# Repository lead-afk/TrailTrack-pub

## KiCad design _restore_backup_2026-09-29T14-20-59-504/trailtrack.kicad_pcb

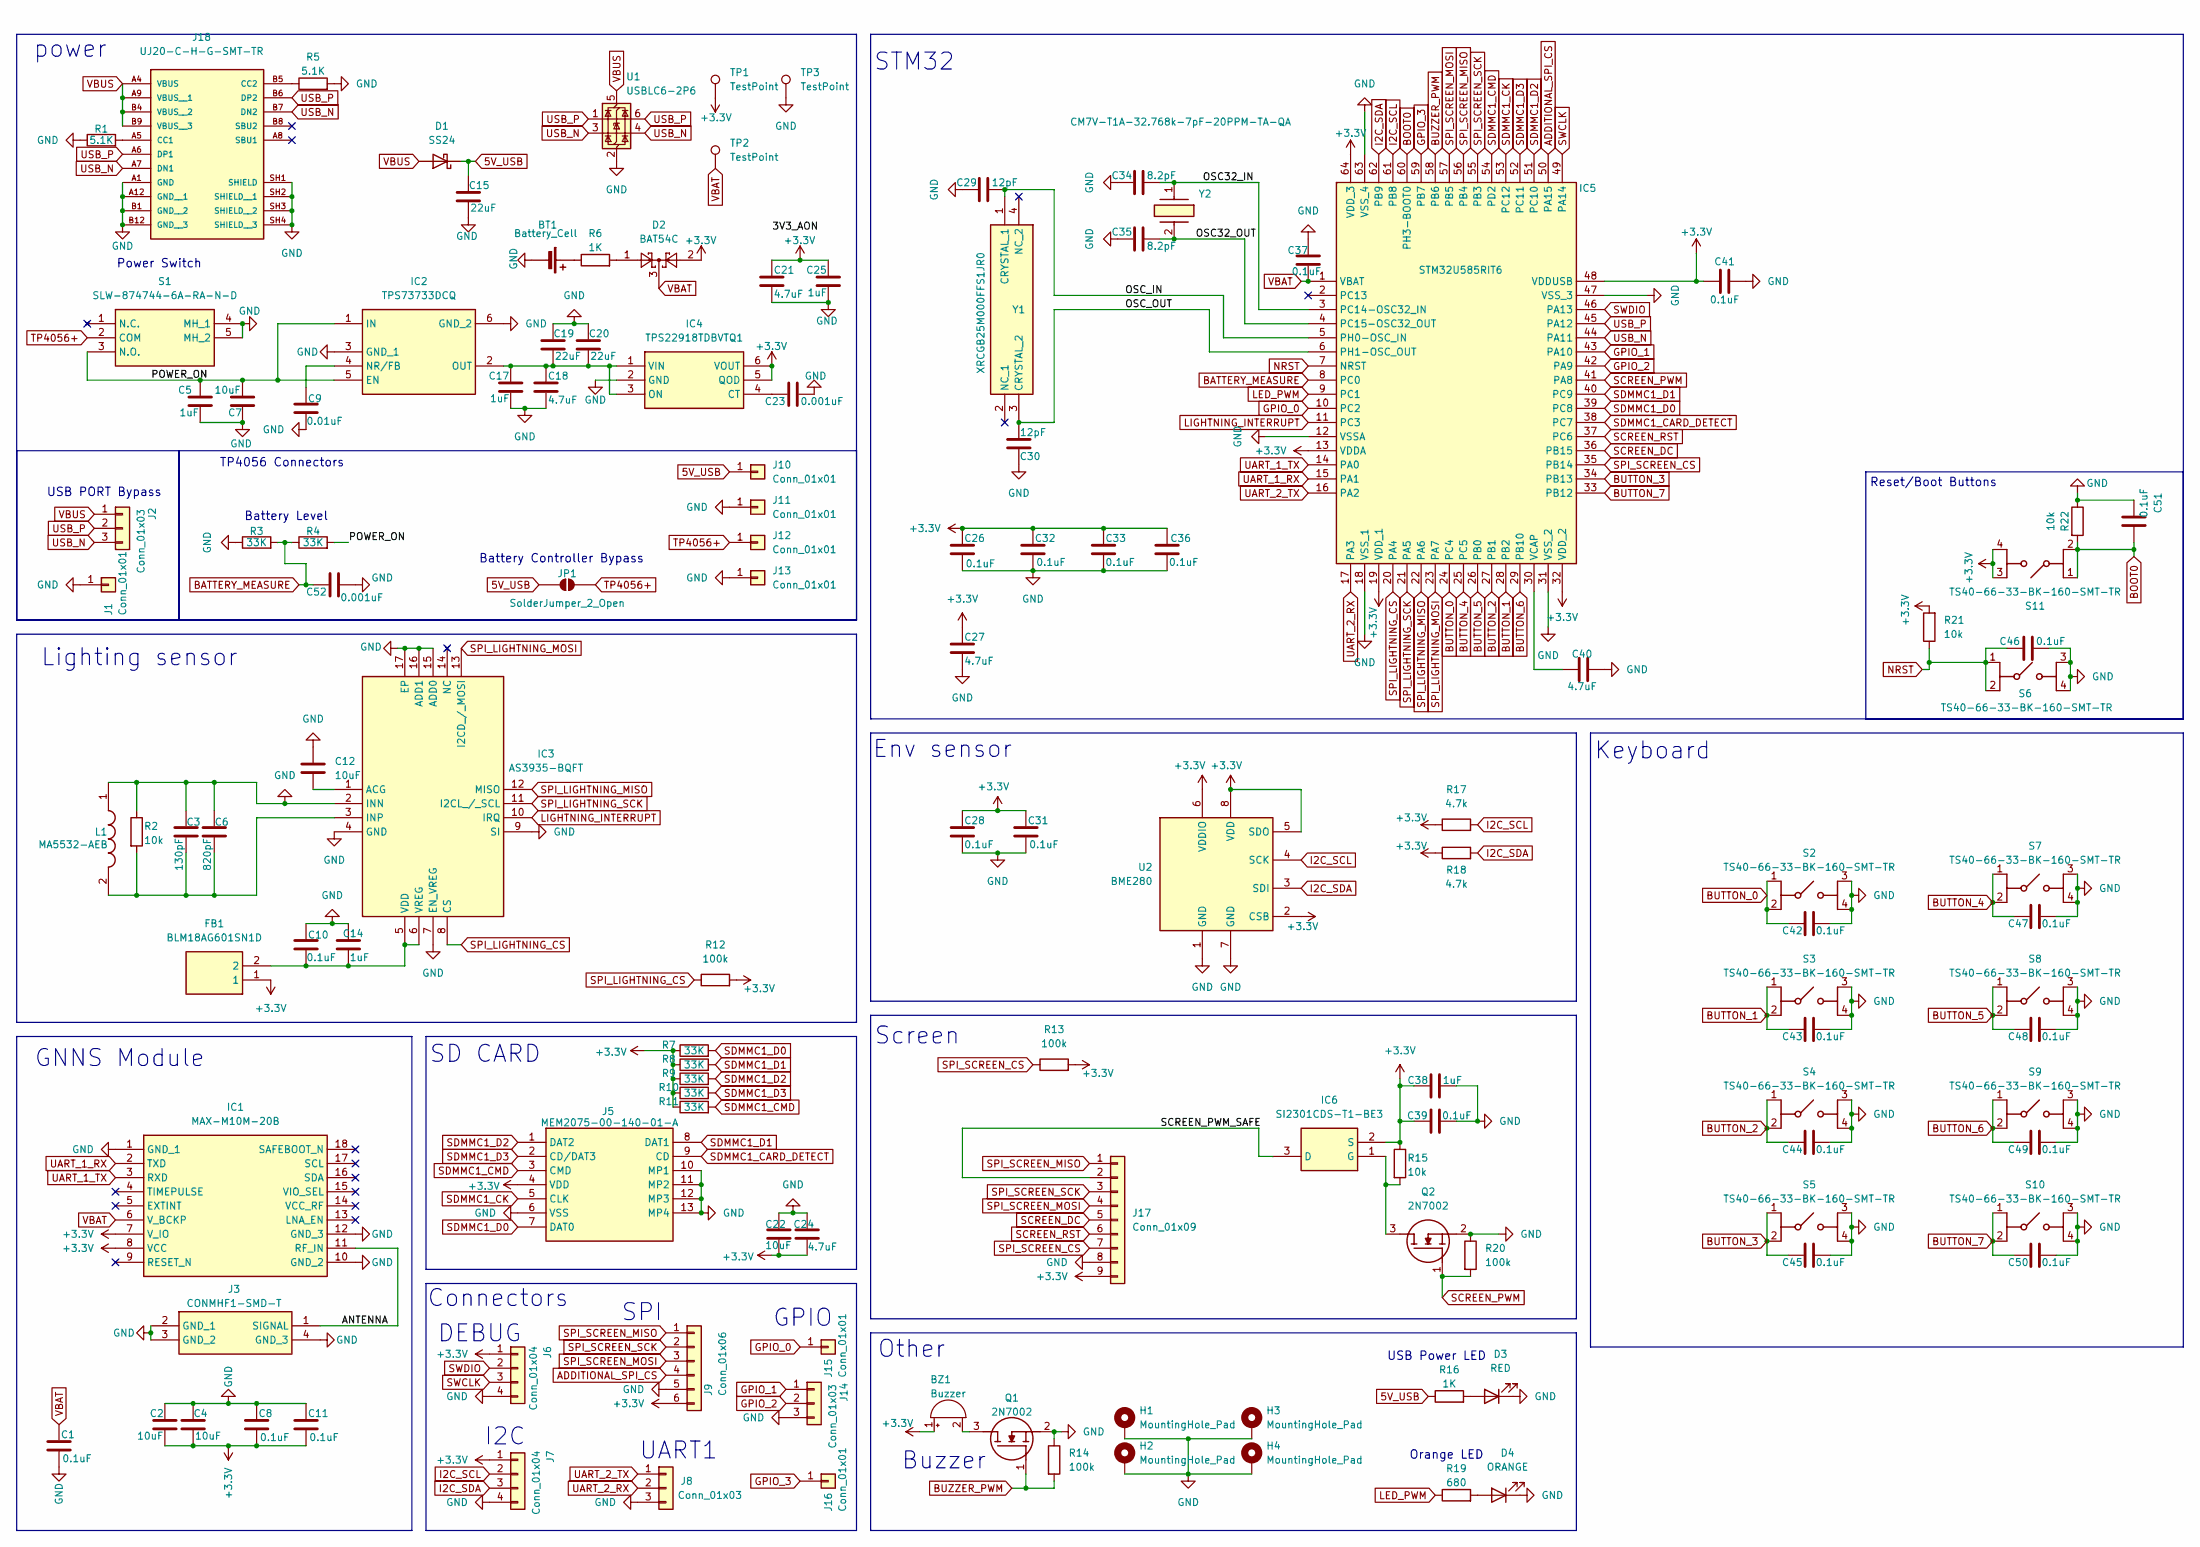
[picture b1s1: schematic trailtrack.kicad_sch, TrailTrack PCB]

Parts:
BT1: Battery_Cell; 1052; Mouser Part Number 534-1052-BH
BZ1: Buzzer; Buzzer_15x7.5RM7.6
C1, C8, C10, C11, C26, C28, C31, C32, C33, C36, C37, C39, C41, C42, C43, C44, C45, C46, C47, C48, C49, C50, C51: 0.1uF; C_0805_2012Metric; Mouser Part Number 81-GCM21BR71E104JA7L
C2, C4, C7, C12, C22: 10uF; C_0805_2012Metric; Mouser Part Number 81-GRM21BC81A106KE8L
C3: 130pF; C_0805_2012Metric; Mouser Part Number 81-GQM21952E131GB12D
C5, C14, C17, C25, C38: 1uF; C_0805_2012Metric; Mouser Part Number 81-GRM40X105K10K
C6: 820pF; C_0805_2012Metric; Mouser Part Number 81-RM21A5C2E821FWA1J
C9: 0.01uF; C_0805_2012Metric; Mouser Part Number 81-GCM2195C1K103FA6D
C15, C19, C20: 22uF; C_0805_2012Metric; Mouser Part Number 81-GRM21BC81A226ME4L
C18, C21, C24, C27, C40: 4.7uF; C_0805_2012Metric; Mouser Part Number 81-GCM21BR71C475KA3L
C23, C52: 0.001uF; C_0805_2012Metric; Mouser Part Number 81-GRM21R72A102JA01D
C29, C30: 12pF; C_0603_1608Metric; Mouser Part Number 81-GCM1885C2A120FA6D
C34, C35: 8.2pF; C_0603_1608Metric; Mouser Part Number 81-GCM1885C2A8R2BA6D
D1: SS24; DIOM5436X244N; Mouser Part Number 821-SS24
D2: BAT54C; SOT-23; Mouser Part Number 637-BAT54C
D3: RED; LED_0805_2012Metric; Mouser Part Number 630-HSMS-C170
D4: ORANGE; LED_0805_2012Metric; Mouser Part Number 630-HSMD-C170
FB1: BLM18AG601SN1D; BLM18SP221SN1B; Mouser Part Number 81-BLM11A601S
H1, H2, H3, H4: MountingHole_Pad; MountingHole_3.2mm_M3_DIN965_Pad
IC1: MAX-M10M-20B; MAXM10M20B; Mouser Part Number 377-MAX-M10M-20B
IC2: TPS73733DCQ; SOT127P706X180-6N; Mouser Part Number 595-TPS73733DCQ
IC3: AS3935-BQFT; QFN65P400X400X80-17N-D; Mouser Part Number 985-AS3935-BQFT
IC4: TPS22918TDBVTQ1; SOT95P280X145-6N; Mouser Part Number 595-TPS22918TDBVTQ1
IC5: STM32U585RIT6; QFP50P1200X1200X160-64N; Mouser Part Number 511-STM32U585RIT6
IC6: SI2301CDS-T1-BE3; SOT95P237X112-3N; Mouser Part Number 78-SI2301CDS-T1-BE3
J1, J10, J11, J12, J13, J15, J16: Conn_01x01; PinHeader_1x01_P2.54mm_Vertical
J2, J8: Conn_01x03; PinHeader_1x03_P2.54mm_Vertical
J3: CONMHF1-SMD-T; CONMHF1SMDT; Mouser Part Number 712-CONMHF1-SMD-T
J5: MEM2075-00-140-01-A; MEM20750014001A; Mouser Part Number 640-MEM20750014001A
J6, J7: Conn_01x04; PinHeader_1x04_P2.54mm_Vertical
J9: Conn_01x06; PinHeader_1x06_P2.54mm_Vertical
J14: Conn_01x03; PinHeader_1x03_P1.27mm_Vertical
J17: Conn_01x09; PinSocket_1x09_P2.54mm_Vertical
J18: UJ20-C-H-G-SMT-TR; CUI_UJ20-C-H-G-SMT-TR; PARTREV 1.01
JP1: SolderJumper_2_Open; SolderJumper-2_P1.3mm_Open_RoundedPad1.0x1.5mm
L1: MA5532-AEB; MA5532AEB; Mouser Part Number 994-MA5532-AE
Q1, Q2: 2N7002; SOT96P240X120-3N; Mouser Part Number 512-2N7002
R1, R5: 5.1K; R_0805_2012Metric; Mouser Part Number 603-RC0805FR-075K1L
R2, R15, R21, R22: 10k; R_0805_2012Metric; Mouser Part Number 603-AC0805DR-0710KL
R3, R4, R7, R8, R9, R10, R11: 33K; R_0805_2012Metric; Mouser Part Number 603-AC0805FR-0733KL
R6, R16: 1K; R_0805_2012Metric; Mouser Part Number 603-AC0805DR-071KL
R12, R13, R14, R20: 100k; R_0805_2012Metric; Mouser Part Number 603-AC0805FR-7W100KL
R17, R18: 4.7k; R_0805_2012Metric; Mouser Part Number 603-AC0805FR-7W4K7L
R19: 680; R_0805_2012Metric; Mouser Part Number 603-AC0805FR-07680RL
S1: SLW-874744-6A-RA-N-D; SLW8747446ARAND; Mouser Part Number 179-SLW8747446ARAND
S2, S3, S4, S5, S6, S7, S8, S9, S10, S11: TS40-66-33-BK-160-SMT-TR; TS406650R260SMTTR; Mouser Part Number 179-TS406633BK160S
TP1, TP2, TP3: TestPoint; TestPoint_Pad_D1.5mm
U1: USBLC6-2P6; SOT-666; Mouser Part Number 511-USBLC6-2P6
U2: BME280; Bosch_LGA-8_2.5x2.5mm_P0.65mm_ClockwisePinNumbering; Mouser Part Number 262-BME280
Y1: XRCGB25M000FFS1JR0; Mouser Part Number 81-XRCGB25M00FFS1JR0
Y2: CM7V-T1A-32.768k-7pF-20PPM-TA-QA; CM7V32768TBQA020; Mouser Part Number 428-201567-MG01

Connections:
5V_USB: C15.1, D1.1 (K), J10.1 (Pin_1_1), JP1.1 (A), R16.1
+3.3V: BZ1.1 (+), C2.2, C4.2, C8.2, C11.2, C21.1, C22.2, C24.2, C25.1, C26.1, C27.1, C28.1, C31.1, C32.1, C33.1, C36.1, C38.2, C39.2, C41.1, D2.2, FB1.1, IC1.7 (V_IO), IC1.8 (VCC), IC4.5 (QOD), IC4.6 (VOUT), IC5.13 (VDDA), IC5.19 (VDD_1), IC5.32 (VDD_2), IC5.48 (VDDUSB), IC5.64 (VDD_3), IC6.2 (S), J5.4 (VDD), J6.1, J7.1, J9.6, J17.9, R7.1, R8.1, R9.1, R10.1, R11.1, R12.2, R13.2, R15.1, R17.1, R18.1, R21.2, S11.3 (NO_1), S11.4 (NO_2), TP1.1 (1_1), U2.2 (CSB), U2.5 (SDO), U2.6 (VDDIO), U2.8 (VDD)
/ANTENNA: IC1.11 (RF_IN), J3.1 (SIGNAL)
/OSC32_IN: C34.2, IC5.3 (PC14-OSC32_IN), Y2.1
/OSC32_OUT: C35.2, IC5.4 (PC15-OSC32_OUT), Y2.2
/OSC_IN: C29.1, IC5.5 (PH0-OSC_IN), Y1.1 (CRYSTAL_1)
/OSC_OUT: C30.1, IC5.6 (PH1-OSC_OUT), Y1.3 (CRYSTAL_2)
/POWER_ON: C5.1, C7.2, IC2.1 (IN), IC2.5 (EN), R4.2, S1.3 (N.O.)
/SCREEN_PWM_SAFE: IC6.3 (D), J17.2
ADDITIONAL_SPI_CS: IC5.50 (PA15), J9.4
BATTERY_MEASURE: C52.2, IC5.8 (PC0), R3.2, R4.1
BOOT0: C51.2, IC5.60 (PH3-BOOT0), R22.2, S11.1 (COM_1), S11.2 (COM_2)
BUTTON_0: C42.1, IC5.24 (PC4), S2.1 (COM_1), S2.2 (COM_2)
BUTTON_1: C43.1, IC5.28 (PB2), S3.1 (COM_1), S3.2 (COM_2)
BUTTON_2: C44.1, IC5.27 (PB1), S4.1 (COM_1), S4.2 (COM_2)
BUTTON_3: C45.1, IC5.34 (PB13), S5.1 (COM_1), S5.2 (COM_2)
BUTTON_4: C47.1, IC5.25 (PC5), S7.1 (COM_1), S7.2 (COM_2)
BUTTON_5: C48.1, IC5.26 (PB0), S8.1 (COM_1), S8.2 (COM_2)
BUTTON_6: C49.1, IC5.29 (PB10), S9.1 (COM_1), S9.2 (COM_2)
BUTTON_7: C50.1, IC5.33 (PB12), S10.1 (COM_1), S10.2 (COM_2)
BUZZER_PWM: IC5.58 (PB6), Q1.1 (G), R14.2
GND: BT1.2 (-), C1.2, C2.1, C3.1, C4.1, C5.2, C6.1, C7.1, C8.1, C9.1, C10.2, C11.1, C12.1, C14.2, C15.2, C17.2, C18.2, C19.1, C20.1, C21.2, C22.1, C23.1, C24.1, C25.2, C26.2, C27.2, C28.2, C29.2, C30.2, C31.2, C32.2, C33.2, C34.1, C35.1, C36.2, C37.1, C38.1, C39.1, C40.2, C41.2, C42.2, C43.2, C44.2, C45.2, C46.2, C47.2, C48.2, C49.2, C50.2, C51.1, C52.1, D3.1 (K), D4.1 (K), H1.1 (1_1), H2.1 (1_1), H3.1 (1_1), H4.1 (1_1), IC1.1 (GND_1), IC1.10 (GND_2), IC1.12 (GND_3), IC2.3 (GND_1), IC2.6 (GND_2), IC3.2 (INN), IC3.4 (GND), IC3.7 (EN_VREG), IC3.9 (SI), IC3.15 (ADD0), IC3.16 (ADD1), IC3.17 (EP), IC4.2 (GND), IC5.12 (VSSA), IC5.18 (VSS_1), IC5.31 (VSS_2), IC5.47 (VSS_3), IC5.63 (VSS_4), J1.1 (Pin_1_1), J3.2 (GND_1), J3.3 (GND_2), J3.4 (GND_3), J5.6 (VSS), J5.10 (MP1), J5.11 (MP2), J5.12 (MP3), J5.13 (MP4), J6.4, J7.4, J8.3, J9.5, J11.1 (Pin_1_1), J13.1 (Pin_1_1), J14.3, J17.8, J18.A1 (GND), J18.A12 (GND__1), J18.B1 (GND__2), J18.B12 (GND__3), J18.SH1 (SHIELD), J18.SH2 (SHIELD__1), J18.SH3 (SHIELD__2), J18.SH4 (SHIELD__3), L1.1, Q1.2 (S), Q2.2 (S), R1.1, R2.1, R3.1, R5.2, R14.1, R20.1, R22.1, S1.4 (MH_1), S1.5 (MH_2), S2.3 (NO_1), S2.4 (NO_2), S3.3 (NO_1), S3.4 (NO_2), S4.3 (NO_1), S4.4 (NO_2), S5.3 (NO_1), S5.4 (NO_2), S6.3 (NO_1), S6.4 (NO_2), S7.3 (NO_1), S7.4 (NO_2), S8.3 (NO_1), S8.4 (NO_2), S9.3 (NO_1), S9.4 (NO_2), S10.3 (NO_1), S10.4 (NO_2), TP3.1 (1_1), U1.2 (GND), U2.1 (GND), U2.7 (GND)
GPIO_0: IC5.10 (PC2), J15.1 (Pin_1_1)
GPIO_1: IC5.43 (PA10), J14.1
GPIO_2: IC5.42 (PA9), J14.2
GPIO_3: IC5.59 (PB7), J16.1 (Pin_1_1)
I2C_SCL: IC5.61 (PB8), J7.2, R17.2, U2.4 (SCK)
I2C_SDA: IC5.62 (PB9), J7.3, R18.2, U2.3 (SDI)
LED_PWM: IC5.9 (PC1), R19.1
LIGHTNING_INTERRUPT: IC3.10 (IRQ), IC5.11 (PC3)
NRST: C46.1, IC5.7 (NRST), R21.1, S6.1 (COM_1), S6.2 (COM_2)
unnamed: BT1.1 (+), R6.1
unnamed: BZ1.2 (-), Q1.3 (D)
unnamed: D2.1, R6.2
unnamed: D3.2 (A), R16.2
unnamed: D4.2 (A), R19.2
unnamed: C9.2, IC2.4 (NR/FB)
unnamed: C17.1, C18.1, C19.2, C20.2, IC2.2 (OUT), IC4.1 (VIN), IC4.3 (ON)
unnamed: C12.2, IC3.1 (ACG)
unnamed: C3.2, C6.2, IC3.3 (INP), L1.2, R2.2
unnamed: C10.1, C14.1, FB1.2, IC3.5 (VDD), IC3.6 (VREG)
unnamed: C23.2, IC4.4 (CT)
unnamed: C40.1, IC5.30 (VCAP)
unnamed: IC6.1 (G), Q2.3 (D), R15.2
unnamed: J18.A5 (CC1), R1.2
unnamed: J18.B5 (CC2), R5.1
SCREEN_DC: IC5.36 (PB15), J17.5
SCREEN_PWM: IC5.41 (PA8), Q2.1 (G), R20.2
SCREEN_RST: IC5.37 (PC6), J17.6
SDMMC1_CARD_DETECT: IC5.38 (PC7), J5.9 (CD)
SDMMC1_CK: IC5.53 (PC12), J5.5 (CLK)
SDMMC1_CMD: IC5.54 (PD2), J5.3 (CMD), R11.2
SDMMC1_D0: IC5.39 (PC8), J5.7 (DAT0), R7.2
SDMMC1_D1: IC5.40 (PC9), J5.8 (DAT1), R8.2
SDMMC1_D2: IC5.51 (PC10), J5.1 (DAT2), R9.2
SDMMC1_D3: IC5.52 (PC11), J5.2 (CD/DAT3), R10.2
SPI_LIGHTNING_CS: IC3.8 (CS), IC5.20 (PA4), R12.1
SPI_LIGHTNING_MISO: IC3.12 (MISO), IC5.22 (PA6)
SPI_LIGHTNING_MOSI: IC3.13 (I2CD_/_MOSI), IC5.23 (PA7)
SPI_LIGHTNING_SCK: IC3.11 (I2CL_/_SCL), IC5.21 (PA5)
SPI_SCREEN_CS: IC5.35 (PB14), J17.7, R13.1
SPI_SCREEN_MISO: IC5.56 (PB4), J9.1, J17.1
SPI_SCREEN_MOSI: IC5.57 (PB5), J9.3, J17.4
SPI_SCREEN_SCK: IC5.55 (PB3), J9.2, J17.3
SWCLK: IC5.49 (PA14), J6.3
SWDIO: IC5.46 (PA13), J6.2
TP4056+: J12.1 (Pin_1_1), JP1.2 (B), S1.2 (COM)
UART_1_RX: IC1.2 (TXD), IC5.15 (PA1)
UART_1_TX: IC1.3 (RXD), IC5.14 (PA0)
UART_2_RX: IC5.17 (PA3), J8.2
UART_2_TX: IC5.16 (PA2), J8.1
USB_N: IC5.44 (PA11), J2.3, J18.A7 (DN1), J18.B7 (DN2), U1.3 (I/O2), U1.4 (I/O2)
USB_P: IC5.45 (PA12), J2.2, J18.A6 (DP1), J18.B6 (DP2), U1.1 (I/O1), U1.6 (I/O1)
VBAT: C1.1, C37.2, D2.3, IC1.6 (V_BCKP), IC5.1 (VBAT), TP2.1 (1_1)
VBUS: D1.2 (A), J2.1, J18.A4 (VBUS), J18.A9 (VBUS__1), J18.B4 (VBUS__2), J18.B9 (VBUS__3), U1.5 (VBUS)

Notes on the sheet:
Keyboard
UART1
SD CARD
Screen
GPIO
I2C
TP4056 Connectors
SPI
Battery Controller Bypass
USB Power LED
GNNS Module
Power Switch
STM32
Other
power
DEBUG
Env sensor
Lighting sensor
USB PORT Bypass
Buzzer
Orange LED
Connectors
Reset/Boot Buttons
Battery Level

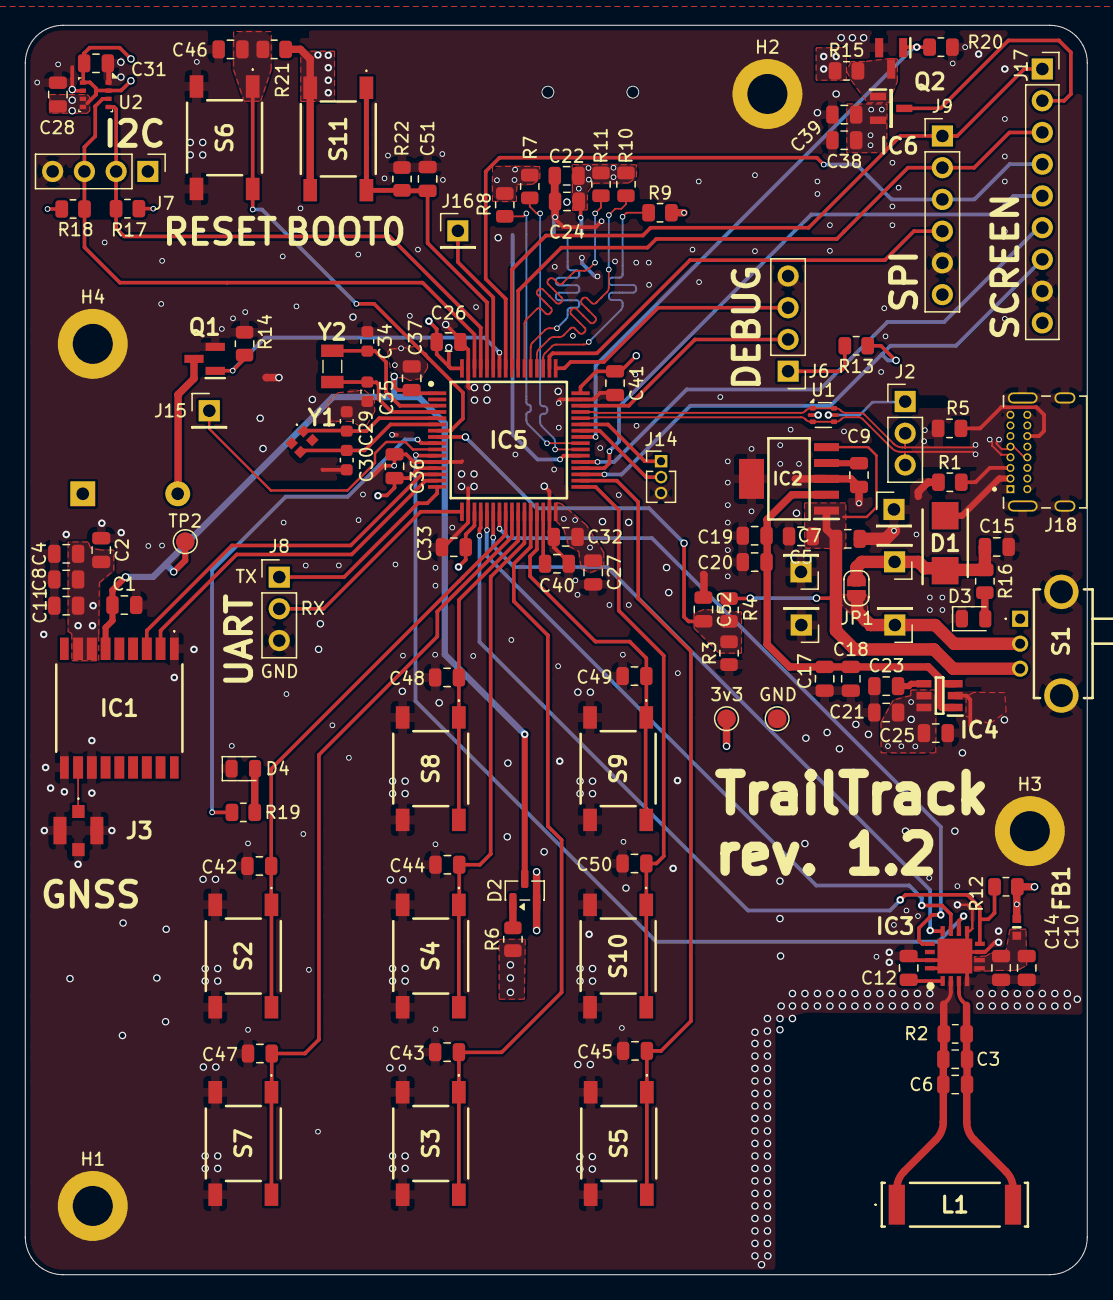
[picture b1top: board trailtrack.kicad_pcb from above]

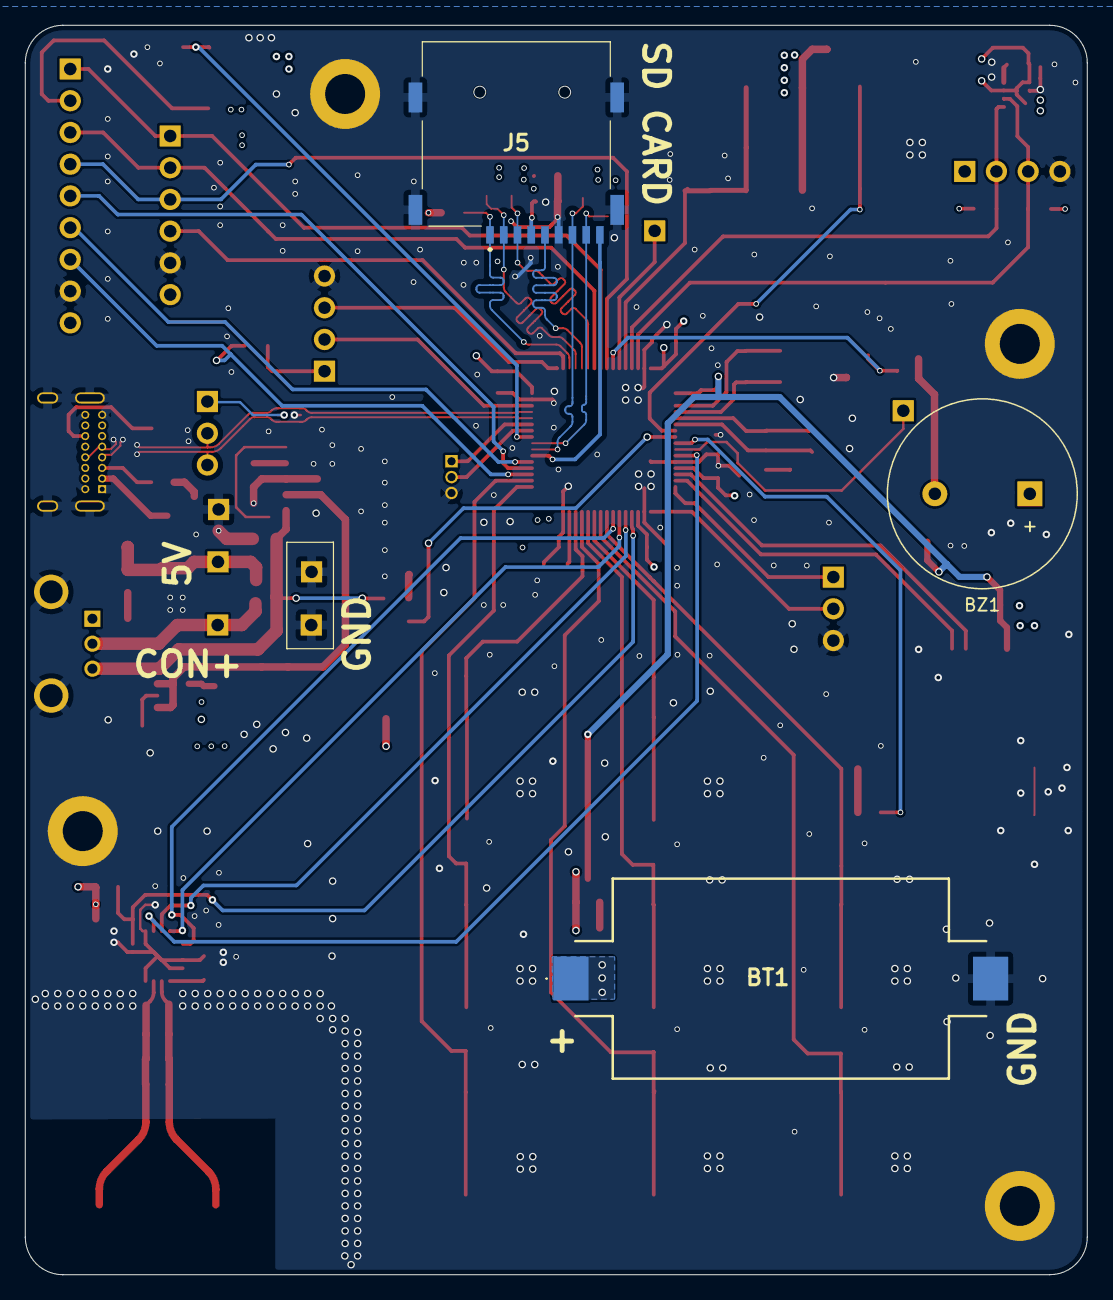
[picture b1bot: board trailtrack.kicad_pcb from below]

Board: 4 copper layers, 85.0 x 100.0 mm, 128 parts (3 on the bottom side), 75 nets.

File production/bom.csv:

Designator,Footprint,Quantity,Value,LCSC Part #
BT1,1052,1,Battery_Cell,
"C1, C11, C12, C26, C28, C31, C32, C33, C36, C38, C39, C41, C43, C44, C45, C46, C47, C48, C49, C50, C51, C52, C53, C9",0805,24,0.1uF,
C10,0805,1,0.01uF,
"C13, C22, C3, C5",0805,4,10uF,
"C14, C23",0805,2,0.001uF,
"C15, C17, C2, C25, C37, C40",0805,6,1uF,
"C16, C19, C20, C6, C8",0805,5,22uF,
"C18, C21, C24, C27, C42",0805,5,4.7uF,
"C29, C30",0603,2,4.7pF,
"C34, C35",0603,2,8.2pF,
C4,0805,1,130pF,
C7,0805,1,820pF,
D1,DIOM5436X244N,1,SS24,
D2,SOT-23,1,BAT54C,
D3,SODFL3816X120N,1,1N4148W,
D4,0805,1,RED,
D5,0805,1,ORANGE,
FB1,BLM18SP221SN1B,1,BLM18AG601SN1D,
IC1,MAXM10M20B,1,MAX-M10M-20B,
IC2,SOT127P706X180-6N,1,TPS73733DCQ,
IC3,QFN65P400X400X80-17N-D,1,AS3935-BQFT,
IC4,SOT95P280X145-6N,1,TPS22918TDBVTQ1,
IC5,QFP50P1200X1200X160-64N,1,STM32U585RIT6,
IC6,SOT95P237X112-3N,1,SI2301CDS-T1-BE3,
J3,CUI_UJ20-C-H-G-SMT-TR,1,UJ20-C-H-G-SMT-TR,
J4,CONMHF1SMDT,1,CONMHF1-SMD-T,
J5,MEM20750014001A,1,MEM2075-00-140-01-A,
L1,MA5532AEB,1,MA5532-AEB,
"Q1, Q2",SOT96P240X120-3N,2,2N7002,
"R1, R4",0805,2,5.1K,
"R10, R11, R3, R5, R7, R8, R9",0805,7,33K,
"R12, R13, R14, R20",0805,4,100k,
"R15, R2, R21, R22",0805,4,10k,
"R16, R6",0805,2,1K,
"R17, R18",0805,2,4.7k,
R19,0805,1,680,
S1,SLW8747446ARAND,1,SLW-874744-6A-RA-N-D,
"S10, S11, S2, S3, S4, S5, S6, S7, S8, S9",TS406650R260SMTTR,10,TS40-66-33-BK-160-SMT-TR,
"TP1, TP2, TP3",TestPoint_Pad_D1.5mm,3,TestPoint,
U1,SOT-666,1,USBLC6-2P6,
U2,Bosch_LGA-8_2.5x2.5mm_P0.65mm_ClockwisePinNumbering,1,BME280,
Y1,XRCGB25M000FFS1JR0,1,XRCGB25M000FFS1JR0,
Y2,CM7V32768TBQA020,1,CM7V-T1A-32.768k-7pF-20PPM-TA-QA,
